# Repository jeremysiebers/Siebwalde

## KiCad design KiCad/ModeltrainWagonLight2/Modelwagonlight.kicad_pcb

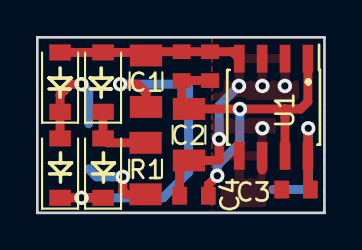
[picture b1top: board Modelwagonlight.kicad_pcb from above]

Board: 2 copper layers, 15.9 x 9.8 mm, 16 parts (0 on the bottom side), 7 nets.

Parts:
C1, C2: 22u; C_1206_3216Metric
C3, C4: 100n; C_0603_1608Metric
D1, D2, D3, D4: STPS0540Z; D_SOD-123
J1, J2, J3, J4: Conn_01x01; Pin_Header_Straight_1x01_Pitch1.00mm
R1: 47E; R_1206_3216Metric
R4: 470E; R_0603_1608Metric
R5: NP; R_0603_1608Metric
U1: LP2951DR; SOIC-8_3.9x4.9mm_P1.27mm

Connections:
GND: C1.2, C2.2, C3.2, C4.2, D3.2, D4.2, R4.1, R5.1, U1.2, U1.3, U1.4, U1.5, U1.6
unnamed: C1.1, D1.1, D2.1, J3.1
unnamed: C2.1, C4.1, R4.2, R5.2, U1.1, U1.7
unnamed: C3.1, J4.1, U1.8
unnamed: D1.2, D3.1, R1.2
unnamed: D2.2, D4.1, J2.1
unnamed: J1.1, R1.1

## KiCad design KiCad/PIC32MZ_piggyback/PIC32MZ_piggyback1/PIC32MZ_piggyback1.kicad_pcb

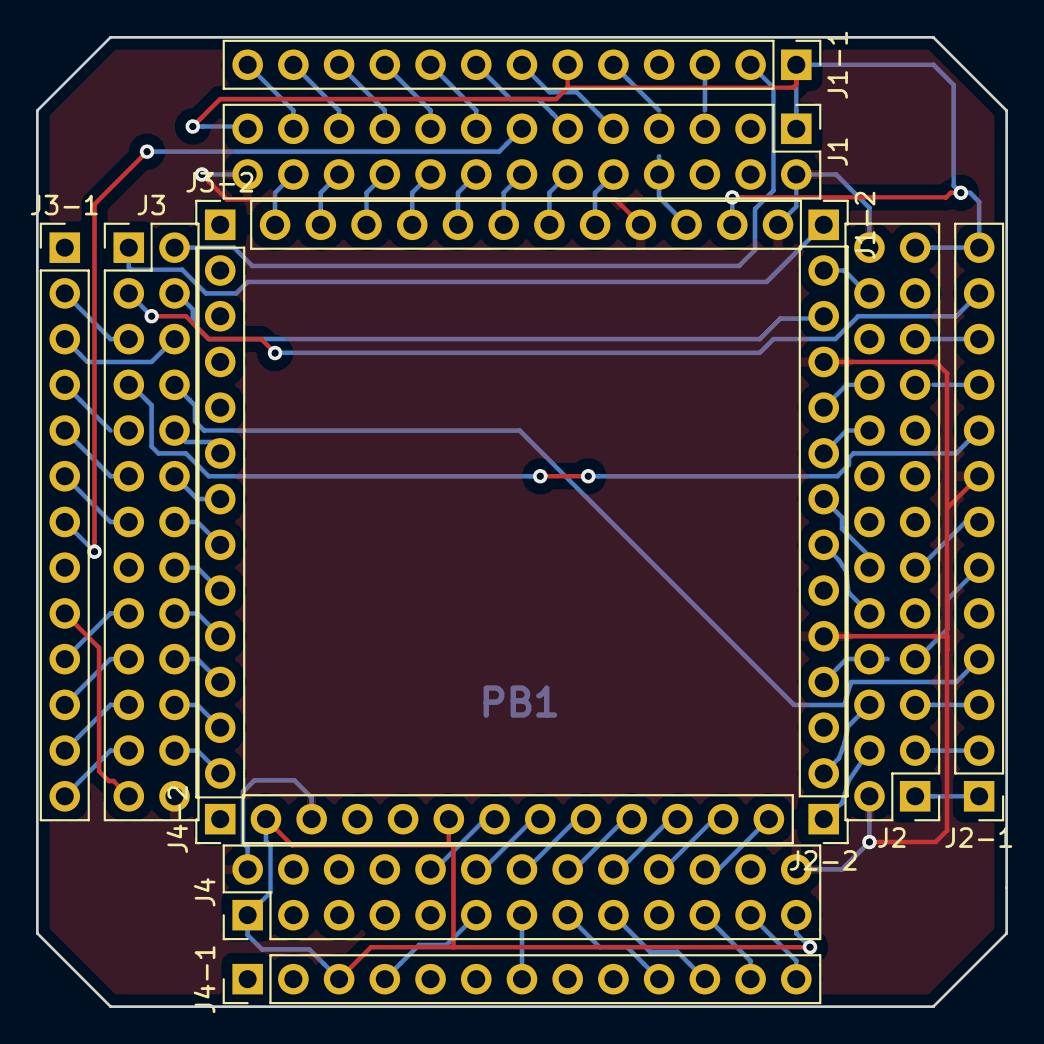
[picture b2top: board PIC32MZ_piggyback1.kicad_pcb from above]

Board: 2 copper layers, 53.8 x 53.8 mm, 12 parts (0 on the bottom side), 72 nets.

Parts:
J1, J2, J3, J4: Conn_02x13_Odd_Even; PinHeader_2x13_P2.54mm_Vertical
J1-1, J1-2, J2-1, J2-2, J3-1, J3-2, J4-1, J4-2: Conn_01x13_Male; PinHeader_1x13_P2.54mm_Vertical

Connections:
/GND: J1.2, J1.26, J1-1.4, J1-2.2, J1-2.5, J2.2, J2.26, J2-1.8, J2-2.5, J2-2.11, J3.26, J3-1.8, J4.2, J4.26, J4-1.6, J4-1.8, J4-2.3
/LED1: J3.5, J3-1.2, J4-1.5
/LED2: J3.6, J3-1.3, J4-2.5
/MCLR: J1.13, J3-1.7
/MCU_MISO: J4.11, J4-1.4
/MCU_MOSI: J4.14, J4-2.9
/MCU_SCK: J4.12, J4-2.8
/RA0: J1.15, J1-1.9
/RA1: J3.16, J3-2.9
/RA2: J4.13, J4-1.7
/RA3: J4.16, J4-2.10
/RA4: J4.15, J4-1.10
/RA5: J4.18, J4-2.11
/RA9: J3.9, J3-1.4
/RA10: J3.10, J3-2.6
/RA14: J4.17, J4-1.11
/RA15: J4.20, J4-2.12
/RB0: J1.23, J1-1.13
/RB1: J1.24, J1-2.13
/RB2: J1.21, J1-1.12
/RB3: J1.22, J1-2.12
/RB4: J1.19, J1-1.11
/RB5: J1.20, J1-2.11
/RB6: J2-1.9, J3.7
/RB7: J2-1.4, J3.8
/RB8: J3.11, J3-1.5
/RB9: J3.12, J3-2.7
/RB10: J3.13, J3-1.6
/RB11: J3.14, J3-2.8
/RB12: J3.17, J3-1.10
/RB13: J3.20, J3-2.11
/RB14: J3.19, J3-1.11
/RB15: J3.22, J3-2.12
/RC1: J1.8, J1-2.4
/RC2: J1.7, J1-1.5
/RC3: J1.10, J1-2.6
/RC4: J1.9, J1-1.7
/RD0: J4.23, J4-1.13
/RD1: J2.1, J2-1.1
/RD2: J2.4, J2-2.1
/RD3: J2.3, J2-1.2
/RD4: J2.7, J2-1.6
/RD5: J2.8, J2-2.4
/RD7: J2.10, J2-2.7
/RD9: J4.22, J4-2.13
/RD10: J4.21, J4-1.12
/RD12: J2.5, J2-1.3
/RD13: J2.6, J2-2.2
/RD14: J3.21, J3-1.12
/RE0: J2.18, J2-2.9
/RE2: J2.21, J2-1.11
/RE3: J2.24, J2-2.13
/RE7: J1.5, J1-1.3
/RE8: J1.18, J1-2.10
/RE9: J1.17, J1-1.10
/RF0: J2.12, J2-2.8
/RF1: J2.11, J2-1.7
/RF3: J4.10, J4-2.7
/RF4: J3.23, J3-1.13
/RF5: J3.24, J3-2.13
/RF12: J3.18, J3-2.10
/RG6: J1.12, J1-2.7
/RG7: J1.11, J1-1.8
/RG8: J1.14, J1-2.8
/RG9: J1.16, J1-2.9
/RG12: J2.19, J2-1.10
/RG14: J2.20, J2-2.10
/RXN: J2-1.12, J3.3
/RXP: J2-2.12, J3.4
/TXN: J1-2.1, J3.1
/TXP: J1-1.2, J3.2
/VCC: J1.1, J1.25, J1-1.1, J1-1.6, J1-2.3, J2.25, J2-1.5, J2-1.13, J2-2.6, J3.25, J3-1.9, J4.1, J4.25, J4-1.3, J4-2.2, J4-2.6

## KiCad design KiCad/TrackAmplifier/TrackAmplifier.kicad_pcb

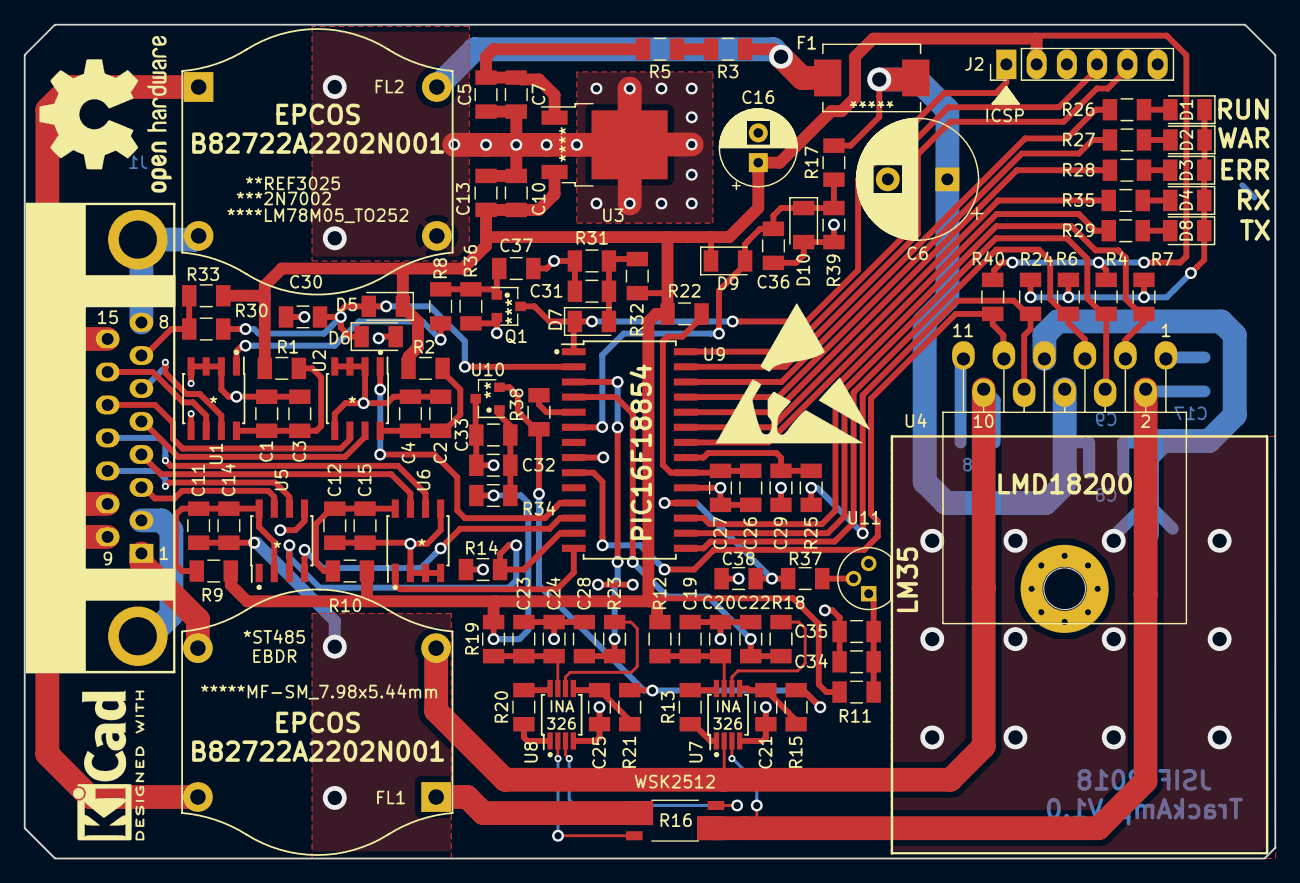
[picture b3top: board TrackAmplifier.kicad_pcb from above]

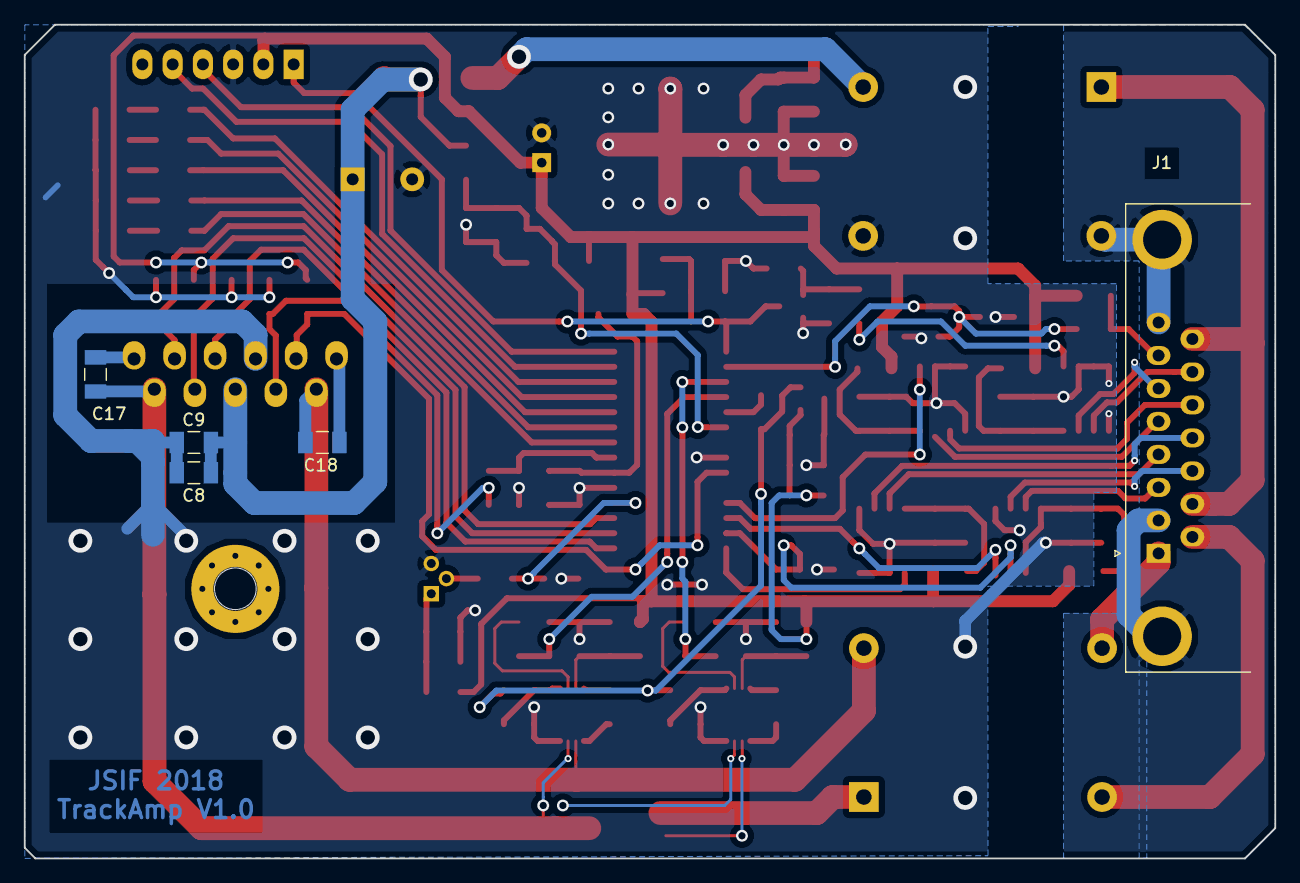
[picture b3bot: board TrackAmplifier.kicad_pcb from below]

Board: 2 copper layers, 105.0 x 70.0 mm, 106 parts (5 on the bottom side), 77 nets.

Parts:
C1, C2, C5, C8, C11, C12, C13, C19, C23, C26, C29, C32, C34, C38: 22u; C_1206_3216Metric
C3, C4, C7, C9, C10, C14, C15, C20, C21, C24, C25, C27, C31, C33, C35, C37: 100n; C_1206_3216Metric
C6: 470u; CP_Radial_D10.0mm_P5.00mm
C16: 100u; CP_Radial_D6.3mm_P2.50mm
C17, C18: 10n; C_1206_3216Metric
C22, C28: 1u; C_1206_3216Metric
C30, C36: 220n; C_1206_3216Metric
D1, D2, D3, D4, D8: LED; LED_1206_3216Metric
D5, D6, D7, D9, D10: 1n4148; D_1206_3216Metric
F1: 3.0A; Fuse_Bourns_MF-SM_7.98x5.44mm
FL1, FL2: EMI_Filter_CMode; Choke_EPCOS_B82722-A2302-N1-22.3x22.7mm
J1: DB15_Male_MountingHoles; DSUB-15_Male_Horizontal_P2.77x2.84mm_EdgePinOffset4.94mm_Ho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
J2: Conn_01x06; PinHeader_1x06_P2.54mm_Vertical
MK1: Mounting_Hole; MountingHole_3.7mm_Pad_Via
Q1: 2N7002; SOT-23
R1, R2, R3, R5, R9, R10, R11, R12, R13, R15, R19, R20, R21, R22, R34, R37, R38: 10E; R_1206_3216Metric
R4, R6, R7, R14: 4K7; R_1206_3216Metric
R8, R18, R23: 100E; R_1206_3216Metric
R16: 0.025; R_Shunt_2512_6332Metric_0.005-0.2
R17, R30: 10k; R_1206_3216Metric
R24: 3K3; R_1206_3216Metric
R25, R33: 1K; R_1206_3216Metric
R26, R27, R28, R29, R35: 330E; R_1206_3216Metric
R31: 100K; R_1206_3216Metric
R32, R36: 10K; R_1206_3216Metric
R39: 50k; R_1206_3216Metric
R40: 4k7; R_1206_3216Metric
U1, U2, U5, U6: ST485EBDR; SOIC-8_3.9x4.9mm_P1.27mm
U3: LM78M05_TO252; TO-252-2
U4: LMD18200; TO-220-11_20.02x17.50mm_P3.4x5.08mm_StaggerOdd_Lead8.45mm_T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
U7, U8: INA326; MSOP-8_3x3mm_P0.65mm
U9: PIC16F18854-SO; SOIC-28W_7.5x17.9mm_P1.27mm
U10: REF3025; SOT-23
U11: LM35-LP; TO-92

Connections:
+5V: C10.2, C13.2, C16.1, D5.1, D9.1, J2.2, R1.2, R2.2, R4.2, R9.2, R10.2, R11.2, R12.1, R19.1, R22.1, R32.1, R33.1, R34.1, R40.1, U3.3
+15V: C5.2, C7.2, R5.2, U3.1
BMF: C22.2, R18.1, U9.4
BRK: R4.1, U4.4, U9.16
CSEN: R24.2, R25.1, U4.8
CSEN_FLT: C29.2, R25.2, U9.21
DIR: R7.2, U4.3, U9.17
GND: C1.1, C2.1, C3.1, C4.1, C5.1, C6.2, C7.1, C8.1, C9.1, C10.1, C11.1, C12.1, C13.1, C14.1, C15.1, C16.2, C19.1, C20.1, C21.1, C22.1, C23.1, C24.1, C25.1, C26.1, C27.1, C28.1, C29.1, C30.1, C31.1, C32.1, C33.1, C34.1, C35.1, C36.1, C37.1, C38.1, D1.1, D2.1, D3.1, D4.1, D6.2, D8.1, D10.2, FL2.4, J2.3, Q1.2, R6.1, R7.1, R14.1, R24.1, R31.2, R36.2, R39.1, U1.2, U1.3, U1.4, U1.5, U2.2, U2.3, U2.4, U2.5, U3.2, U4.7, U5.5, U6.2, U6.3, U6.4, U6.5, U7.4, U8.4, U9.8, U9.19, U10.3, U11.3
GNDD: FL2.3, J1.0, J1.2, J1.8
ICSPCLK: J2.5, U9.27
ICSPDAT: J2.4, U9.28
ID: C30.2, D5.2, D6.1, R30.2, U9.2
ID_R: J1.7, R30.1, R33.2
unnamed: C1.2, C3.2, R1.1, U1.8
unnamed: C2.2, C4.2, R2.1, U2.8
unnamed: C6.1, C8.2, C9.2, F1.1, R17.2, U4.6
unnamed: C11.2, C14.2, R9.1, U5.2, U5.8
unnamed: C12.2, C15.2, R10.1, U6.8
unnamed: C17.1, U4.1
unnamed: C18.2, U4.11
unnamed: C19.2, C20.2, R12.2, U7.7
unnamed: C21.2, R15.2, U7.5
unnamed: C23.2, C24.2, R19.2, U8.7
unnamed: C25.2, R21.2, U8.5
unnamed: C26.2, C27.2, R22.2, U9.20
unnamed: C31.2, D7.2, R31.1, R32.2
unnamed: C32.2, C33.2, R34.2, U10.1
unnamed: C34.2, C35.2, R11.1, U11.1
unnamed: C37.2, Q1.1, R8.2, R36.1
unnamed: D1.2, R26.2
unnamed: D2.2, R27.2
unnamed: D3.2, R28.2
unnamed: D4.2, R35.1
unnamed: D8.2, R29.2
unnamed: FL1.1, R16.4
unnamed: FL2.1, J1.10, J1.15
unnamed: R3.2, R5.1
unnamed: R8.1, U1.1
unnamed: R13.1, U7.1
unnamed: R13.2, U7.8
unnamed: R18.2, U7.6
unnamed: R20.1, U8.1
unnamed: R20.2, U8.8
unnamed: R23.2, U8.6
unnamed: R26.1, U9.26
unnamed: R27.1, U9.25
unnamed: R28.1, U9.24
unnamed: R29.1, U9.22
unnamed: R35.2, U9.23
unnamed: R37.1, U11.2
unnamed: R38.2, U9.5
OCC: C28.2, R23.1, U9.3
OCC1: R16.2, U8.3
OCC2: R16.3, U8.2
PWM: R6.2, U4.5, U9.15
PWM1: C17.2, R16.1, U4.2, U7.3
PWM2: C18.1, FL1.3, U4.10, U7.2
PWMO1: FL1.2, J1.9
PWMO2: FL1.4, J1.1
RST: D7.1, J2.1, Q1.3, U9.1
RX: U6.1, U9.14
RX_A: J1.12, U6.6
RX_B: J1.4, U6.7
Reset_A: J1.14, U1.6
Reset_B: J1.6, U1.7
SYNC: U2.1, U9.11
Sync_A: J1.13, U2.6
Sync_B: J1.5, U2.7
TEMP: C38.2, R37.2, U9.18
THFLG: R40.2, U4.9, U9.9
TX: U5.4, U9.12
TX_A: J1.11, U5.6
TX_B: J1.3, U5.7
TX_ENA: R14.2, U5.3, U9.13
VREF: R15.1, R21.1, R38.1, U10.2
Vbus_flt: F1.2, FL2.2, R3.1
Vlm: C36.2, D9.2, D10.1, R17.1, R39.2, U9.6

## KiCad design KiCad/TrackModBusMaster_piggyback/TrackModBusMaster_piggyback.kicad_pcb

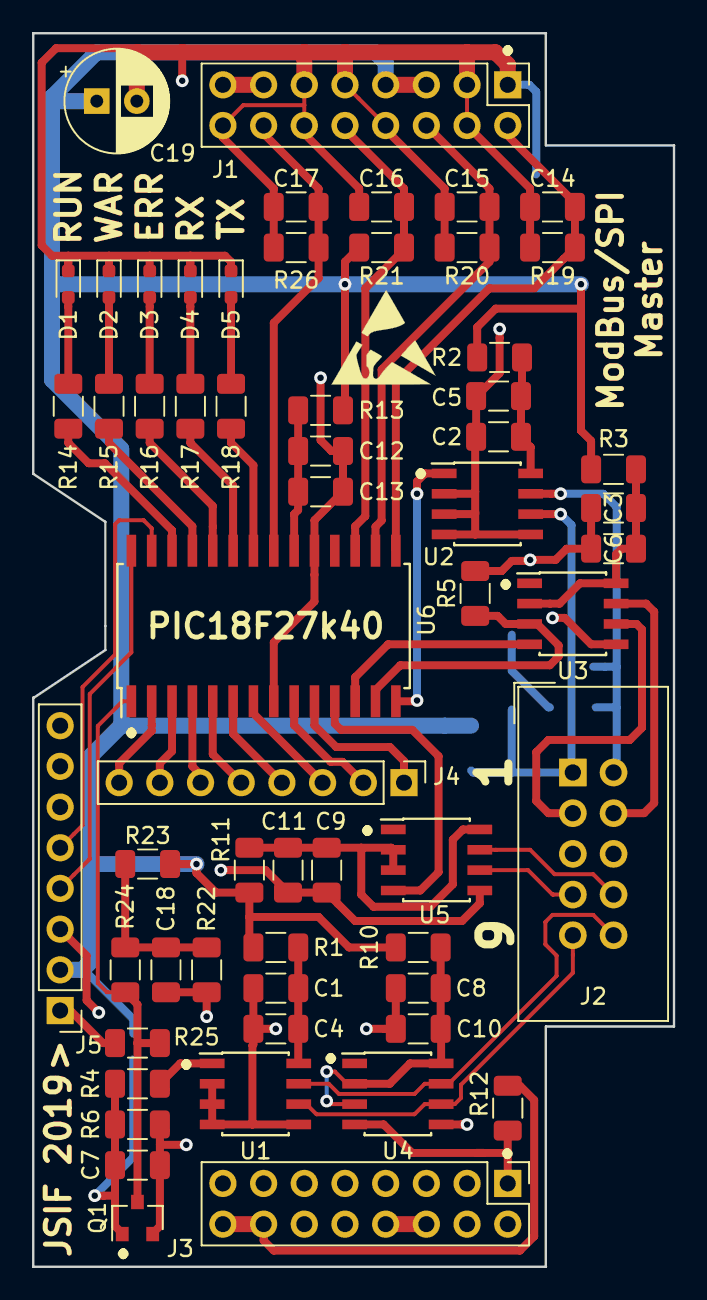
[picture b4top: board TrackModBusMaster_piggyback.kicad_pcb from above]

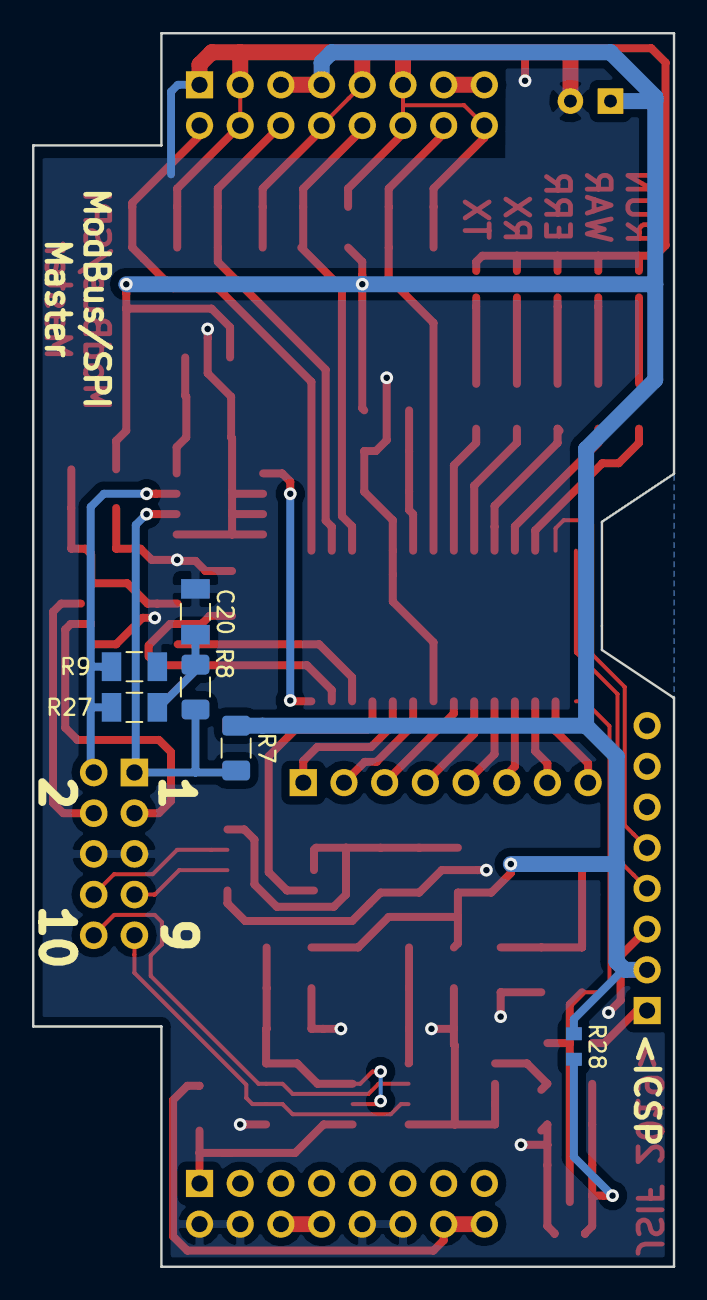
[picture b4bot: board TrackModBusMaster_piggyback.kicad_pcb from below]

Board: 2 copper layers, 40.0 x 77.0 mm, 65 parts (6 on the bottom side), 54 nets.

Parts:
C1, C2, C3, C8, C9, C12, C18: 4.7u; C_1206_3216Metric
C4, C5, C6, C7, C10, C11, C13, C20: 100n; C_1206_3216Metric
C14, C15, C16, C17: 22p; C_1206_3216Metric
C19: 220u; CP_Radial_D6.3mm_P2.50mm
D1, D4, D5: LED GR; LED_0.8x0.8
D2: LED YE; LED_0.8x0.8
D3: LED RD; LED_0.8x0.8
J1, J3: Conn_02x08_Top_Bottom; PinHeader_2x08_P2.54mm_Vertical
J2: Conn_02x05_Odd_Even; IDC-Header_2x05_P2.54mm_Vertical
J4, J5: Conn_01x08; PinHeader_1x08_P2.54mm_Vertical
Q1: NTR5103NT1G; SOT-23
R1, R2, R3, R10, R11, R13: 0E; R_1206_3216Metric
R4, R7, R9: 1k; R_1206_3216Metric
R5, R12, R19, R20, R21, R26: 4k99; R_1206_3216Metric
R6, R23: 10k; R_1206_3216Metric
R8, R27: 60E; R_1206_3216Metric
R14, R15, R16, R17, R18: 300E; R_1206_3216Metric
R22: 110k; R_1206_3216Metric
R24, R25: 470E; R_1206_3216Metric
R28: NP; R_0603_1608Metric
U1, U2, U3, U4, U5: ST485EBDR; SOIC-8_3.9x4.9mm_P1.27mm
U6: PIC18F25K40; SOIC-28W_7.5x17.9mm_P1.27mm

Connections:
+3.3VP: J1.13, J1.15
+3V3: J3.14, J3.16, R12.1
+5V: C19.1, J1.5, J1.7, J5.2, R1.1, R2.1, R3.1, R7.2, R10.1, R11.1, R13.1, R21.1, R23.1, R28.1
+5VP: J3.6, J3.8
GND: C1.2, C2.2, C3.2, C4.2, C5.2, C6.2, C7.2, C8.2, C9.2, C10.2, C11.2, C12.2, C13.2, C14.2, C15.2, C16.2, C17.2, C18.2, C19.2, C20.2, D1.1, D2.1, D3.1, D4.1, D5.1, J1.1, J1.3, J1.4, J1.8, J1.9, J1.11, J1.12, J1.16, J2.5, J2.6, J3.2, J3.4, J3.10, J3.12, J5.3, Q1.2, R5.2, R6.2, R9.1, R19.2, R20.2, R22.2, R26.2, U1.2, U1.3, U1.4, U1.5, U2.2, U2.3, U2.4, U2.5, U3.5, U4.5, U5.5, U6.8, U6.19
ICSPCLK: J5.5, U6.27
ICSPDAT: J5.4, U6.28
unnamed: C1.1, C4.1, R1.2, U1.8
unnamed: C2.1, C5.1, R2.2, U2.8
unnamed: C3.1, C6.1, R3.2, U3.2, U3.8
unnamed: C7.1, Q1.1, R4.1, R6.1, R28.2
unnamed: C8.1, C10.1, R10.2, U4.2, U4.3, U4.8
unnamed: C9.1, C11.1, R11.2, U5.2, U5.3, U5.8
unnamed: C12.1, C13.1, R13.2, U6.20
unnamed: C18.1, R22.1, R23.2, R24.2
unnamed: C20.1, R8.2, R27.2
unnamed: D1.2, R14.1
unnamed: D2.2, R15.1
unnamed: D3.2, R16.1
unnamed: D4.2, R17.1
unnamed: D5.2, R18.1
unnamed: J4.1, U6.10
unnamed: J4.2, U6.9
unnamed: J4.3, U6.7
unnamed: J4.4, U6.6
unnamed: J4.5, U6.5
unnamed: J4.6, U6.4
unnamed: J4.7, U6.3
unnamed: J4.8, U6.2
unnamed: R4.2, U1.1
unnamed: R14.2, U6.26
unnamed: R15.2, U6.25
unnamed: R16.2, U6.24
unnamed: R17.2, U6.23
unnamed: R18.2, U6.22
Reset: Q1.3, R24.1, R25.1, U6.1
Reset_A: J2.9, U1.6, U4.6
Reset_B: J2.10, U1.7, U4.7
Reset_Out: J3.1, R12.2, U4.4
Rx: U2.1, U6.14
Rx_A: J2.1, R7.1, R8.1, U2.6
Rx_B: J2.2, R9.2, R27.1, U2.7
SCK1: C17.1, J1.14, R26.1, U6.21
SDI: C14.1, J1.2, R19.1, U6.15
SDO: C15.1, J1.6, R20.1, U6.16
SS1: C16.1, J1.10, R21.2, U6.17
Sync: U5.4, U6.11
Sync_A: J2.7, U5.6
Sync_B: J2.8, U5.7
Tx: U3.4, U6.12
Tx_A: J2.3, U3.6
Tx_B: J2.4, U3.7
Tx_En: R5.1, U3.3, U6.13
Vpp: J5.1, R25.2
